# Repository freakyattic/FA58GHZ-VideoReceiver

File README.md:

# FA58GHZ-VideoReceiver

This is the repository for the FA58GHZ ( FreakyAttic 5.8GHZ ) RF Video Receiver Module with the following characteristics:

- Video OSD with interactive menus to configure all module functions.
- 40 channels (5 bands), supporting most of the 5.8GHz video transmitters
- Battery monitor with audio warning alarm.
- Fan output for lens defogging with multiple options and timers
- Posibility to add and extra RF video receiver for Diversity operation.
- Three user button to handle all the functions.
- Open software and hardware platform, based on Arduino and Eagle PCB, no need for licences and fees!!

This module it is going to be integrated in a FPV goggles like the Fatshark base SD, but It could be used for many other platforms.

# ---PROJECT UNDER DEVELOPMENT ---

# FA58GHZ Schematic

# Few pictures

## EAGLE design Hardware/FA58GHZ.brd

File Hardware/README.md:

# FA58GHZ Hardware

The hardware is developed using Eagle CAD software, using the Freeware license.

# Schematic

# PCB

# ---PROJECT UNDER DEVELOPMENT---

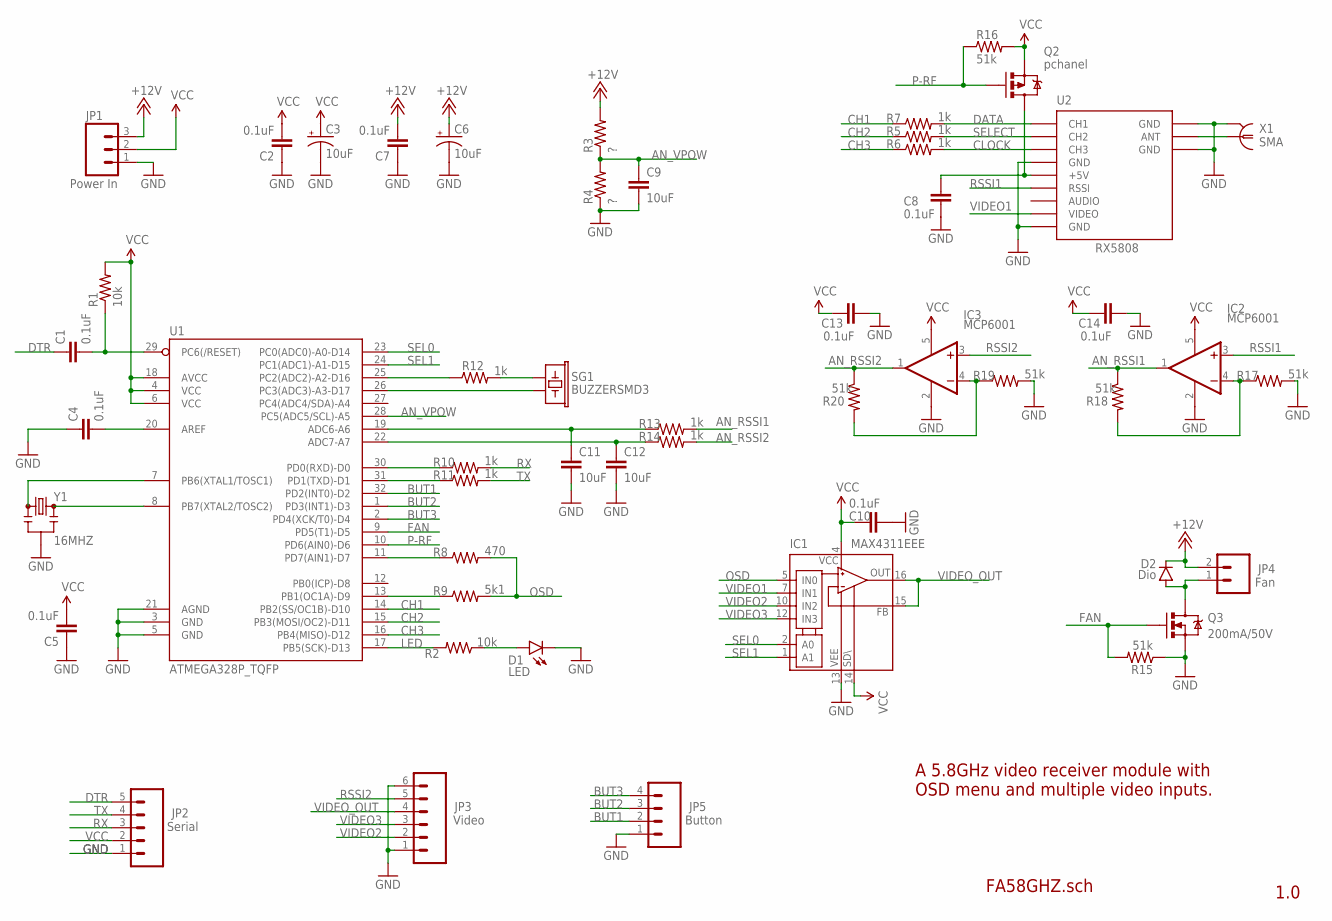
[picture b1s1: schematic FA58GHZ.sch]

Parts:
C1, C2, C4, C5, C7, C8, C10, C13, C14: 0.1uF; C0603
C3, C6: 10uF; EIA3216
C9, C11, C12: 10uF; 0603-CAP
D1: LED; LED-0603
D2: Dio; SOD-323
IC1: MAX4311EEE; QSOP16
IC2, IC3: MCP6001; SC70-5
JP1: Power In; 1X03-1.27MM-OFFSET
JP2: Serial; 1X05-1.27MM-OFFSET
JP3: Video; 1X06-1.27MM-OFFSET
JP4: Fan; 1X02-1.27MM-OFFSET
JP5: Button; 1X04-1.27MM-OFFSET
Q2: pchanel; SOT23-3
Q3: 200mA/50V; SOT23-3
R1, R2: 10k; R0603
R3, R4: ?; R0603
R5, R6, R7, R10, R11, R12, R13, R14: 1k; R0603
R8: 470; R0603
R9: 5k1; R0603
R15, R16, R17, R18, R19, R20: 51k; R0603
SG1: BUZZERSMD3; BUZZER-12X12X3MM
U1: ATMEGA328P_TQFP; TQFP32-08
U2: RX5808
X1: SMA; SMA-PCB
Y1: 16MHZ; RESONATOR-SMD

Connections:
+12V: C6.A (+), C7.2, D2.C, JP1.3, JP4.2, R3.2
AN_RSSI1: IC2.1 (OUT), R13.2, R18.1
AN_RSSI2: IC3.1 (OUT), R14.2, R20.1
AN_VPOW: C9.1, R3.1, R4.2, U1.28 (PC5(ADC5/SCL)-A5)
BUT1: JP5.2, U1.32 (PD2(INT0)-D2)
BUT2: JP5.3, U1.1 (PD3(INT1)-D3)
BUT3: JP5.4, U1.2 (PD4(XCK/T0)-D4)
CH1: R7.1, U1.14 (PB2(SS/OC1B)-D10)
CH2: R5.1, U1.15 (PB3(MOSI/OC2)-D11)
CH3: R6.1, U1.16 (PB4(MISO)-D12)
CLOCK: R6.2, U2.P$7 (CH3)
DATA: R7.2, U2.P$9 (CH1)
DTR: C1.1, JP2.5
FAN: Q3.1 (G), R15.2, U1.9 (PD5(T1)-D5)
GND: C2.1, C3.C (-), C4.1, C5.1, C6.C (-), C7.1, C8.2, C9.2, C10.1, C11.2, C12.2, C13.2, C14.2, D1.C, IC1.13 (V-), IC2.2 (V-), IC3.2 (V-), JP1.1, JP2.1, JP3.1, JP3.6, JP5.1, Q3.2 (S), R4.1, R15.1, R17.2, R19.2, U1.3 (GND), U1.5 (GND), U1.21 (AGND), U2.P$1 (GND), U2.P$6 (GND), U2.P$10 (GND), U2.P$12 (GND), X1.P$1@1 (2), X1.P$1@2 (2), Y1.2
LED: R2.2, U1.17 (PB5(SCK)-D13)
unnamed: U1.8 (PB7(XTAL2/TOSC2)), Y1.3
unnamed: U1.7 (PB6(XTAL1/TOSC1)), Y1.1
unnamed: C1.2, R1.1, U1.29 (PC6(/RESET))
unnamed: C4.2, U1.20 (AREF)
unnamed: D1.A, R2.1
unnamed: R8.1, U1.11 (PD7(AIN1)-D7)
unnamed: R9.1, U1.13 (PB1(OC1A)-D9)
unnamed: R10.1, U1.30 (PD0(RXD)-D0)
unnamed: R11.1, U1.31 (PD1(TXD)-D1)
unnamed: R12.1, U1.25 (PC2(ADC2)-A2-D16)
unnamed: SG1.2, U1.26 (PC3(ADC3)-A3-D17)
unnamed: R12.2, SG1.1
unnamed: D2.A, JP4.1, Q3.3 (D)
unnamed: IC2.4 (-IN), R17.1, R18.2
unnamed: IC3.4 (-IN), R19.1, R20.2
unnamed: U2.P$11 (ANT), X1.P$2 (1)
unnamed: C12.1, R14.1, U1.22 (ADC7-A7)
unnamed: C11.1, R13.1, U1.19 (ADC6-A6)
unnamed: C8.1, Q2.3 (D), U2.P$5 (+5V)
OSD: IC1.5 (IN0), R8.2, R9.2
P-RF: Q2.1 (G), R16.1, U1.10 (PD6(AIN0)-D6)
RSSI1: IC2.3 (+IN), U2.P$4 (RSSI)
RSSI2: IC3.3 (+IN), JP3.5
RX: JP2.3, R10.2
SEL0: IC1.2 (A0), U1.23 (PC0(ADC0)-A0-D14)
SEL1: IC1.1 (A1), U1.24 (PC1(ADC1)-A1-D15)
SELECT: R5.2, U2.P$8 (CH2)
TX: JP2.4, R11.2
VCC: C2.2, C3.A (+), C5.2, C10.2, C13.1, C14.1, IC1.4 (V+), IC1.14 (!SHDN), IC2.5 (V+), IC3.5 (V+), JP1.2, JP2.2, Q2.2 (S), R1.2, R16.2, U1.4 (VCC), U1.6 (VCC), U1.18 (AVCC)
VIDEO1: IC1.7 (IN1), U2.P$2 (VIDEO)
VIDEO2: IC1.10 (IN2), JP3.2
VIDEO3: IC1.12 (IN3), JP3.3
VIDEO_OUT: IC1.15 (FB), IC1.16 (OUT), JP3.4

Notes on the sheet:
A 5.8GHz video receiver module with OSD menu and multiple video inputs.
1.0
FA58GHZ.sch

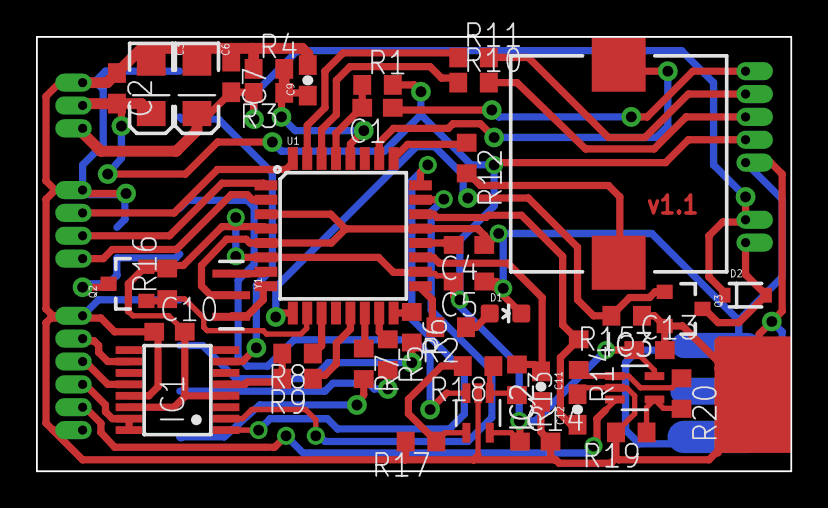
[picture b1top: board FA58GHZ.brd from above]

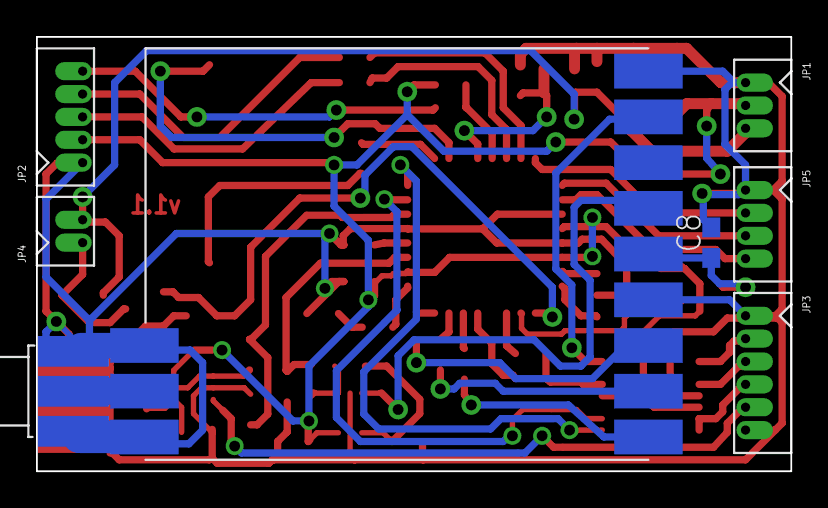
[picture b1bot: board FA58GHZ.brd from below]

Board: 2 copper layers, 41.9 x 24.1 mm, 51 parts (8 on the bottom side), 49 nets.

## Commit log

2015-11-06 First Backup
2015-11-07 Backup: Working in the Schematic, Footprints and PCB
2015-11-08 Finish with the board Schematic, starting to code functions.
2015-11-09 Backup: Firmware: Working the RF Module channel set
2015-11-09 Firmware Backup: Implementing the OSD Menus and Key functions
2015-11-10 Firmware Backup: Implementing menus funcitons, problems with the RF module, backup to make tests.
2015-11-10 Firmware Backup: Current video files work, but there is a compiler bug, if headers are changed the video library doesnt work.
2015-11-10 Firmware Backup: Manual channel setup working with Scann function.
2015-11-10 FIRMWARE Backup: - RF Functions working, need to make PCB for final test. - Need to implement FAN functions.
2015-11-10 Adding Pictures/Screens Version 1.0B
2015-11-11 FIRMWARE VERSION: 1.01 Beta -Fan menus and hardware functions implemented.
2015-11-12 Backup: Implemented OSD menu for Battery Monitor, needs to test it. - Modifications for the schematic - working on the PCB
2015-11-13 Backup: PCB routing finished, need to run DRC
2015-11-13 -Routing finished and DRC passed with approved warnings
2015-11-13 HARDWARE VERSION 1.0: CNC PCB prototype for testing.
2015-11-14 BOARD VER: 1.1 - Fix footprints and pinout problems with RF
2015-11-14 Adding schematic Pictures/FA58GHZ_PCB.jpg
2015-11-14 Adding pictres

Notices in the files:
parts and their libraries:
SparkFun-Capacitors: Licensing: Creative Commons ShareAlike 4.0 International - https://creativecommons.org/licenses/by-sa/4.0
